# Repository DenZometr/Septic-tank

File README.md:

Контроллер состояния септика для Топас.

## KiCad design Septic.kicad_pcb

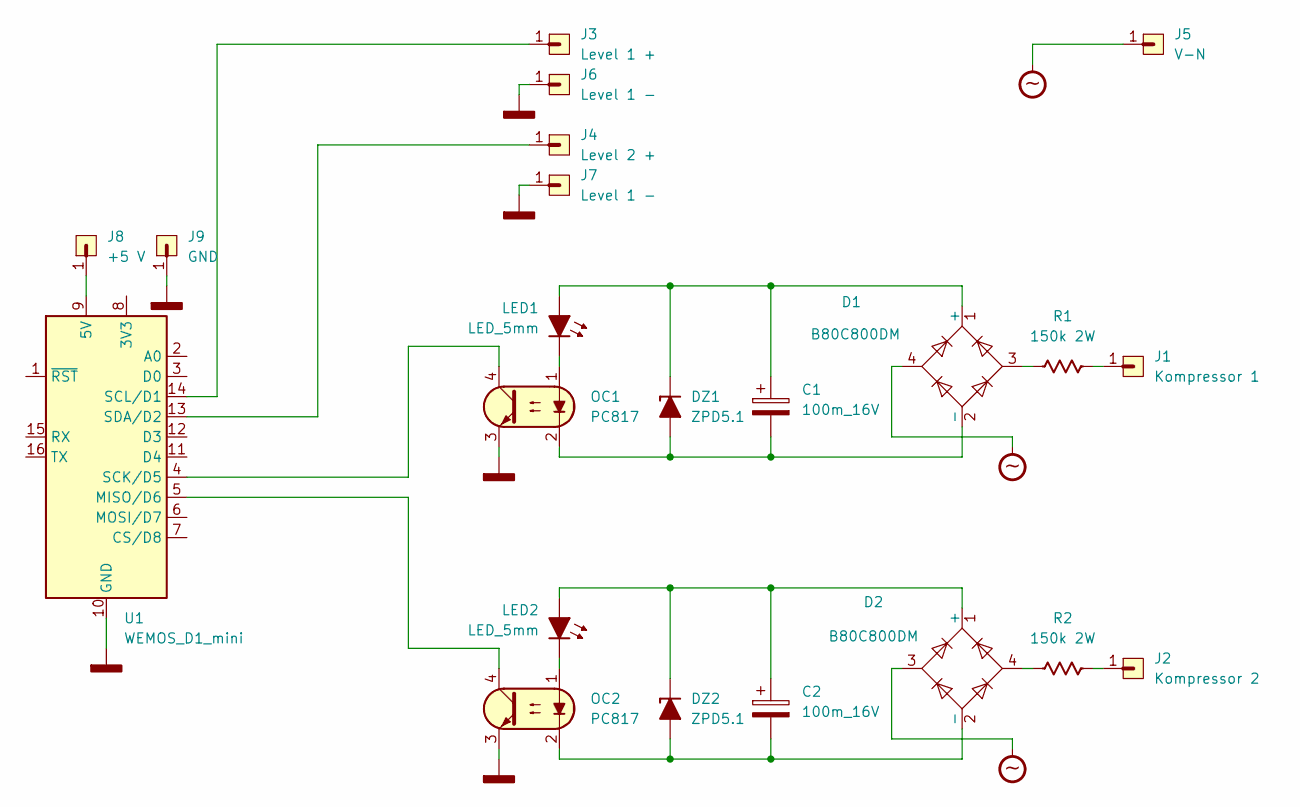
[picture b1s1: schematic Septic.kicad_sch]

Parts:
C1, C2: 100m_16V; CP_Radial_D7.5mm_P2.50mm
D1, D2: B80C800DM; Diode_Bridge_DIP-4_W7.62mm_P5.08mm
DZ1, DZ2: ZPD5.1; D_DO-35_SOD27_P2.54mm_Vertical_KathodeUp_Zener
J1: Kompressor 1; PinHeader_1x01_P2.54mm_Vertical
J2: Kompressor 2; PinHeader_1x01_P2.54mm_Vertical
J3: Level 1 +; PinHeader_1x01_P2.54mm_Vertical
J4: Level 2 +; PinHeader_1x01_P2.54mm_Vertical
J5: V-N; PinHeader_1x01_P2.54mm_Vertical
J6, J7: Level 1 -; PinHeader_1x01_P2.54mm_Vertical
J8: +5 V; PinHeader_1x01_P2.54mm_Vertical
J9: GND; PinHeader_1x01_P2.54mm_Vertical
LED1, LED2: LED_5mm; LED_D5.0mm
OC1, OC2: PC817; DIP-4_W7.62mm_LongPads
R1, R2: 150k 2W; R_Axial_DIN0204_L3.6mm_D1.6mm_P5.08mm_Vertical
U1: WEMOS_D1_mini; WEMOS_D1_mini_light

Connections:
unnamed: C1.1, D1.1 (+), DZ1.1 (K), LED1.2 (A)
unnamed: C1.2, D1.2 (-), DZ1.2 (A), OC1.2
unnamed: D1.3, R1.2
unnamed: C2.1, D2.1 (+), DZ2.1 (K), LED2.2 (A)
unnamed: C2.2, D2.2 (-), DZ2.2 (A), OC2.2
unnamed: D2.4, R2.2
unnamed: J1.1, R1.1
unnamed: J2.1, R2.1
unnamed: LED1.1 (K), OC1.1
unnamed: LED2.1 (K), OC2.1
unnamed: J8.1, U1.9 (5V)
unnamed: OC2.4, U1.5 (MISO/D6)
unnamed: OC1.4, U1.4 (SCK/D5)
unnamed: J3.1, U1.14 (SCL/D1)
unnamed: J4.1, U1.13 (SDA/D2)
V-GND: J6.1, J7.1, J9.1, OC1.3, OC2.3, U1.10 (GND)
V-N: D1.4, D2.3, J5.1

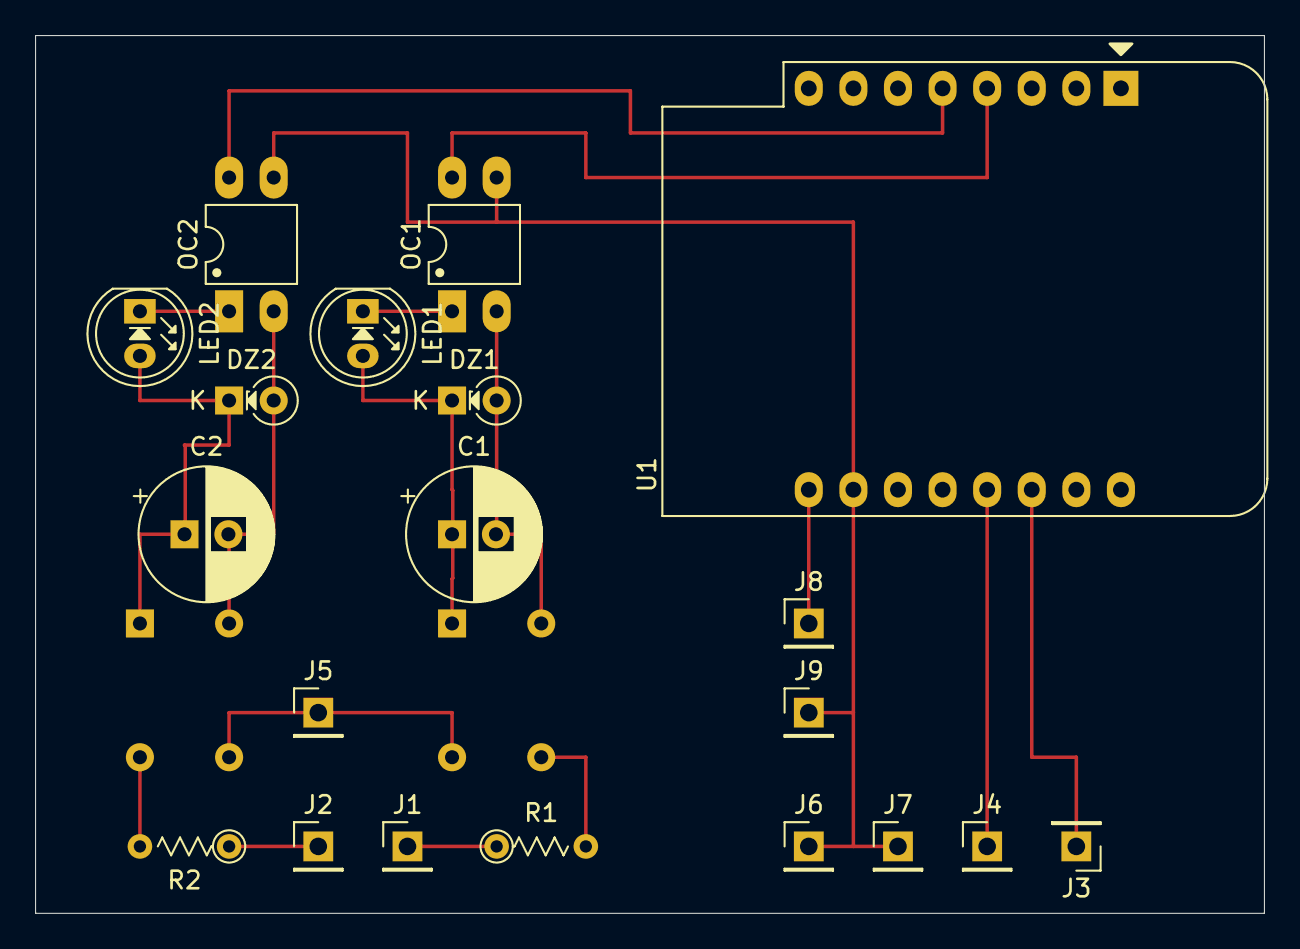
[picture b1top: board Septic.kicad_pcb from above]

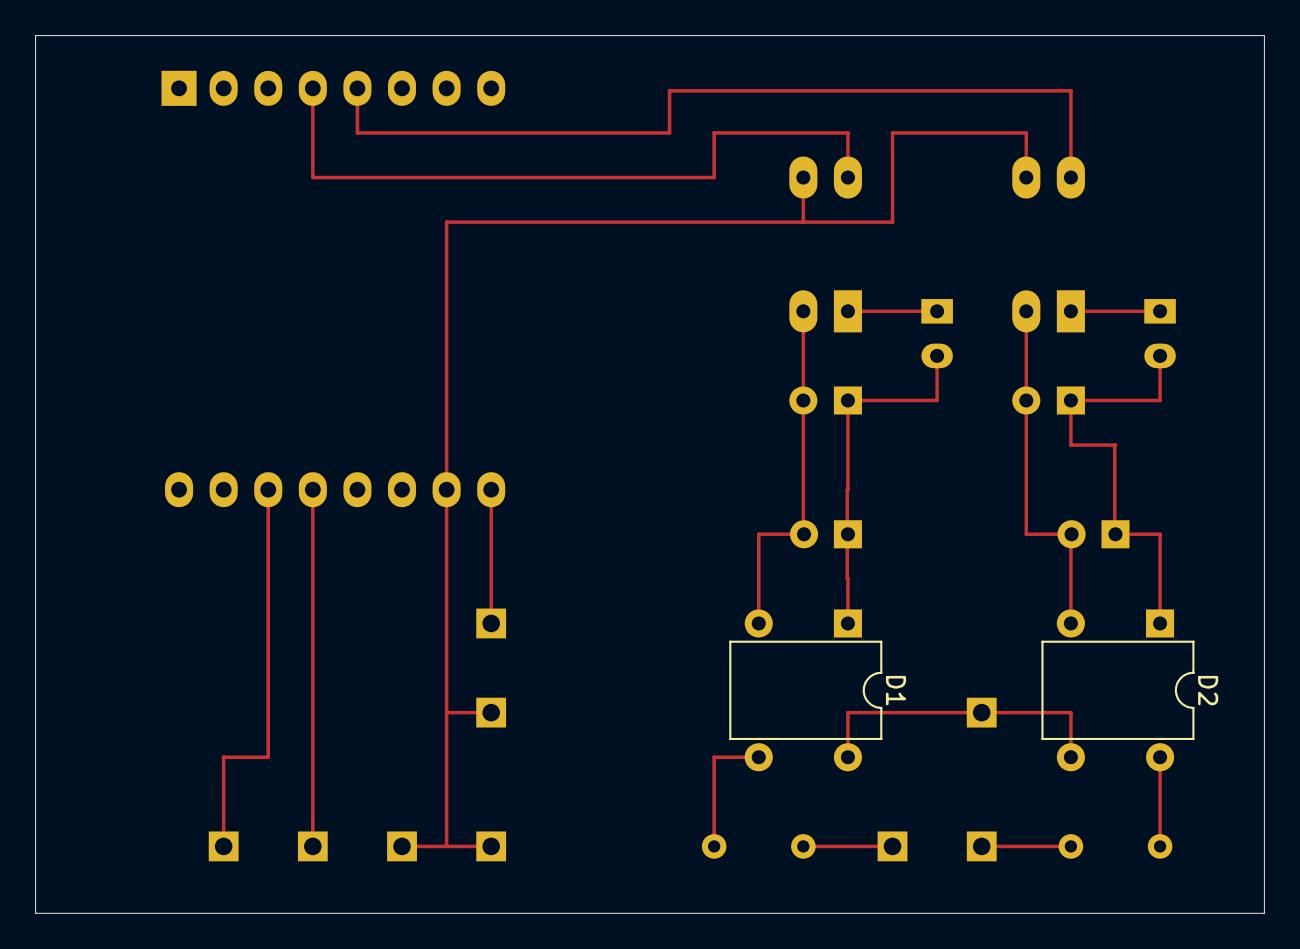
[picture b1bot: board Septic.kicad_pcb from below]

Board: 2 copper layers, 70.0 x 50.0 mm, 22 parts (2 on the bottom side), 17 nets.

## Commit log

2026-04-08 Add files via upload
    Схема контроллера состояния септика.
2026-04-08 Add files via upload
    Плата для контроллера септика в KiCad.
2026-04-08 Add files via upload
    Схема контроллера септика в KiCad.
2026-04-08 Add files via upload
    Схема септика.
